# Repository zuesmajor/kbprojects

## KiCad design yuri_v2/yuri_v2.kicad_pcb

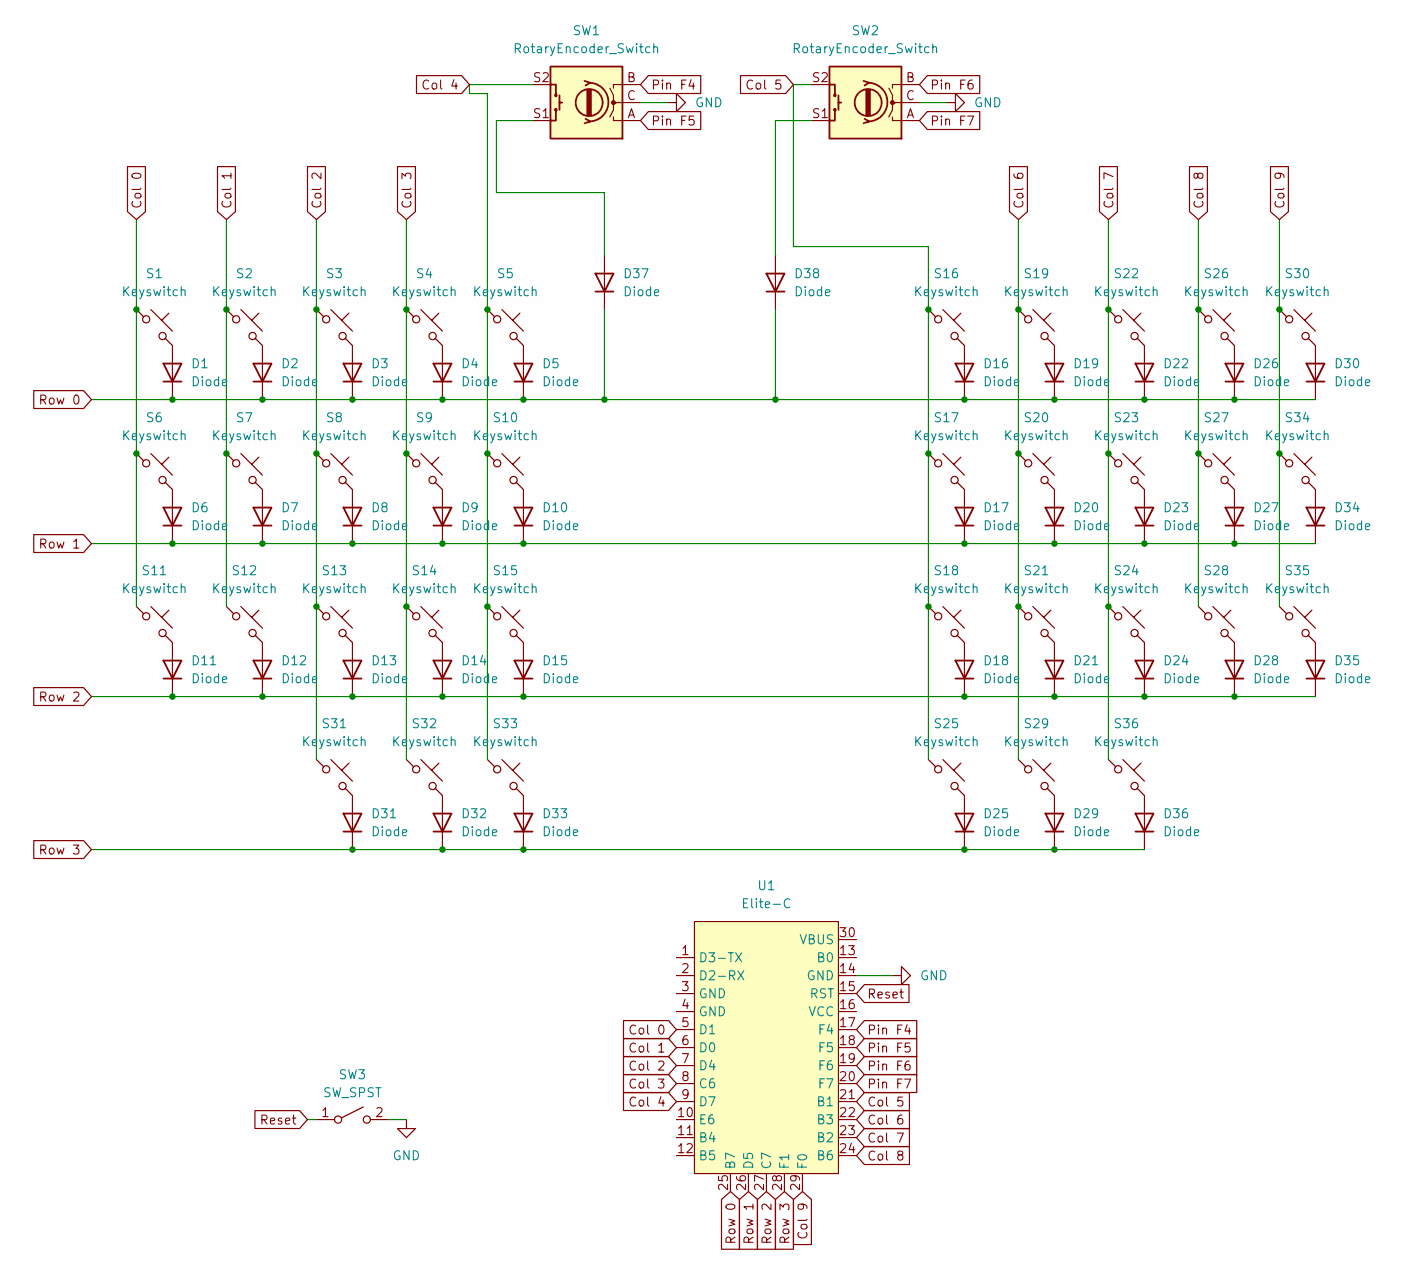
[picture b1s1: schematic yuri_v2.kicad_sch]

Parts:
D1, D2, D3, D4, D5, D6, D7, D8, D9, D10, D11, D12, D13, D14, D15, D16, D17, D18, D19, D20, D21, D22, D23, D24, D25, D26, D27, D28, D29, D30, D31, D32, D33, D34, D35, D36, D37, D38: Diode; Diode_SOD-123
S1, S2, S3, S4, S5, S6, S7, S8, S9, S10, S11, S12, S13, S14, S15, S16, S17, S18, S19, S20, S21, S22, S23, S24, S25, S26, S27, S28, S29, S30, S31, S32, S33, S34, S35, S36: Keyswitch; MX_PCB_1.00u
SW1, SW2: RotaryEncoder_Switch; RotaryEncoder_EC11
SW3: SW_SPST; PushSwitch
U1: Elite-C; Elite-C_ACH

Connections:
Col 0: S1.1, S6.1, S11.1, U1.5 (D1)
Col 1: S2.1, S7.1, S12.1, U1.6 (D0)
Col 2: S3.1, S8.1, S13.1, S31.1, U1.7 (D4)
Col 3: S4.1, S9.1, S14.1, S32.1, U1.8 (C6)
Col 4: S5.1, S10.1, S15.1, S33.1, SW1.S2, U1.9 (D7)
Col 5: S16.1, S17.1, S18.1, S25.1, SW2.S2, U1.21 (B1)
Col 6: S19.1, S20.1, S21.1, S29.1, U1.22 (B3)
Col 7: S22.1, S23.1, S24.1, S36.1, U1.23 (B2)
Col 8: S26.1, S27.1, S28.1, U1.24 (B6)
Col 9: S30.1, S34.1, S35.1, U1.29 (F0)
GND: SW1.C, SW2.C, SW3.2 (B), U1.14 (GND); also elsewhere on the board
unnamed: D1.2 (A), S1.2
unnamed: D2.2 (A), S2.2
unnamed: D3.2 (A), S3.2
unnamed: D4.2 (A), S4.2
unnamed: D5.2 (A), S5.2
unnamed: D6.2 (A), S6.2
unnamed: D7.2 (A), S7.2
unnamed: D8.2 (A), S8.2
unnamed: D9.2 (A), S9.2
unnamed: D10.2 (A), S10.2
unnamed: D11.2 (A), S11.2
unnamed: D12.2 (A), S12.2
unnamed: D13.2 (A), S13.2
unnamed: D14.2 (A), S14.2
unnamed: D15.2 (A), S15.2
unnamed: D16.2 (A), S16.2
unnamed: D17.2 (A), S17.2
unnamed: D18.2 (A), S18.2
unnamed: D19.2 (A), S19.2
unnamed: D20.2 (A), S20.2
unnamed: D21.2 (A), S21.2
unnamed: D22.2 (A), S22.2
unnamed: D23.2 (A), S23.2
unnamed: D24.2 (A), S24.2
unnamed: D25.2 (A), S25.2
unnamed: D26.2 (A), S26.2
unnamed: D27.2 (A), S27.2
unnamed: D28.2 (A), S28.2
unnamed: D29.2 (A), S29.2
unnamed: D30.2 (A), S30.2
unnamed: D31.2 (A), S31.2
unnamed: D32.2 (A), S32.2
unnamed: D33.2 (A), S33.2
unnamed: D34.2 (A), S34.2
unnamed: D35.2 (A), S35.2
unnamed: D36.2 (A), S36.2
unnamed: D37.2 (A), SW1.S1
unnamed: D38.2 (A), SW2.S1
Pin F4: SW1.B, U1.17 (F4)
Pin F5: SW1.A, U1.18 (F5)
Pin F6: SW2.B, U1.19 (F6)
Pin F7: SW2.A, U1.20 (F7)
Reset: SW3.1 (A), U1.15 (RST); also elsewhere on the board
Row 0: D1.1 (K), D2.1 (K), D3.1 (K), D4.1 (K), D5.1 (K), D16.1 (K), D19.1 (K), D22.1 (K), D26.1 (K), D30.1 (K), D37.1 (K), D38.1 (K), U1.25 (B7)
Row 1: D6.1 (K), D7.1 (K), D8.1 (K), D9.1 (K), D10.1 (K), D17.1 (K), D20.1 (K), D23.1 (K), D27.1 (K), D34.1 (K), U1.26 (D5)
Row 2: D11.1 (K), D12.1 (K), D13.1 (K), D14.1 (K), D15.1 (K), D18.1 (K), D21.1 (K), D24.1 (K), D28.1 (K), D35.1 (K), U1.27 (C7)
Row 3: D25.1 (K), D29.1 (K), D31.1 (K), D32.1 (K), D33.1 (K), D36.1 (K), U1.28 (F1)

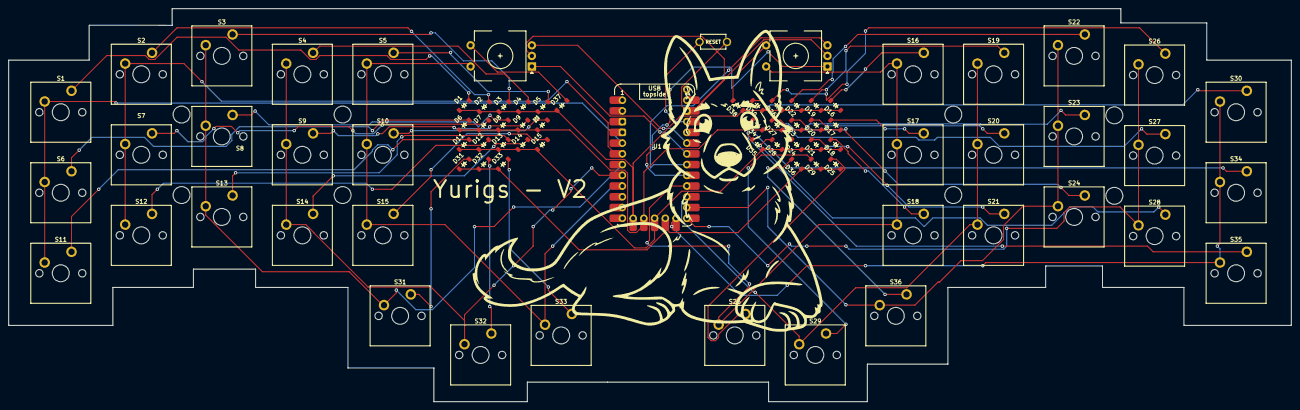
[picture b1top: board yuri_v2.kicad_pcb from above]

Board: 2 copper layers, 303.4 x 93.0 mm, 78 parts (0 on the bottom side), 58 nets.

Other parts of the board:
SW4: SW_PUSH; TACT_SWITCH_TVBP06

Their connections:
GND: SW4.2; also elsewhere on the board
Reset: SW4.1; also elsewhere on the board

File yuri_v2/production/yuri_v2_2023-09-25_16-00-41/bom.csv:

Designator,Footprint,Quantity,Value,LCSC Part #
"D1, D10, D11, D12, D13, D14, D15, D16, D17, D18, D19, D2, D20, D21, D22, D23, D24, D25, D26, D27, D28, D29, D3, D30, D31, D32, D33, D34, D35, D36, D37, D38, D4, D5, D6, D7, D8, D9",Diode_SOD-123,38,Diode,
"S1, S10, S11, S12, S13, S14, S15, S16, S17, S18, S19, S2, S20, S21, S22, S23, S24, S25, S26, S27, S28, S29, S3, S30, S31, S32, S33, S34, S35, S36, S4, S5, S6, S7, S8, S9",MX_PCB_1.00u,36,Keyswitch,
"SW1, SW2",RotaryEncoder_EC11,2,RotaryEncoder_Switch,
SW4,TACT_SWITCH_TVBP06,1,SW_PUSH,

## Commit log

2023-09-06 initial
2023-09-06 renaming the project folder name
2023-09-06 reverting the folder name
2023-09-06 syncing with what is live
2023-09-25 added a submitted order
2023-10-03 adding the traditional 84 key but for somereason i named it 104
2023-10-23 adding des keycaps bambu project
2023-10-25 organizing files and added the case stl
